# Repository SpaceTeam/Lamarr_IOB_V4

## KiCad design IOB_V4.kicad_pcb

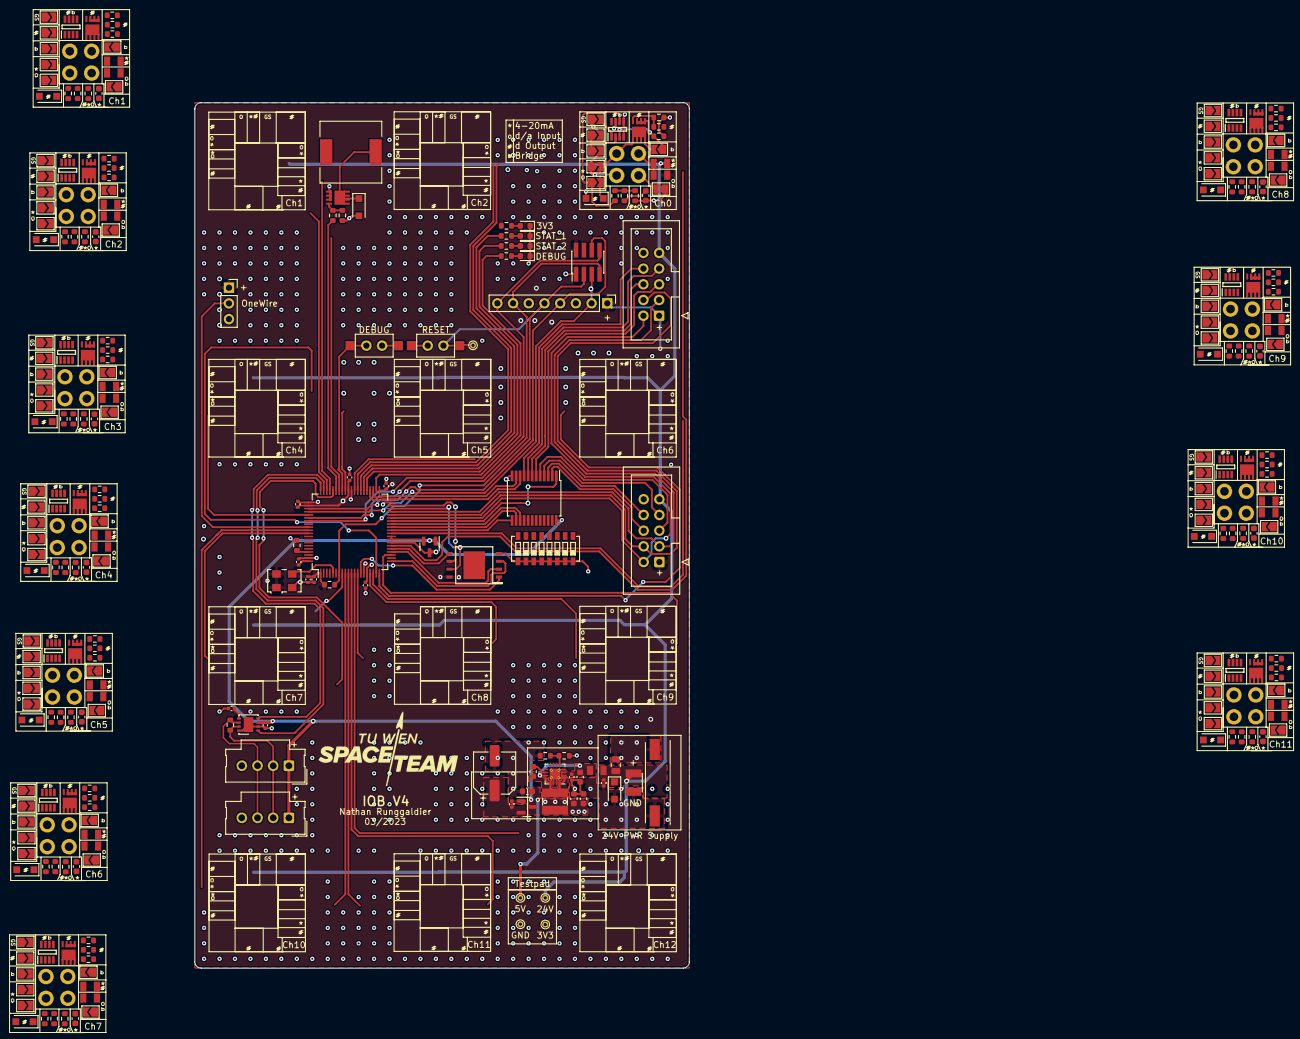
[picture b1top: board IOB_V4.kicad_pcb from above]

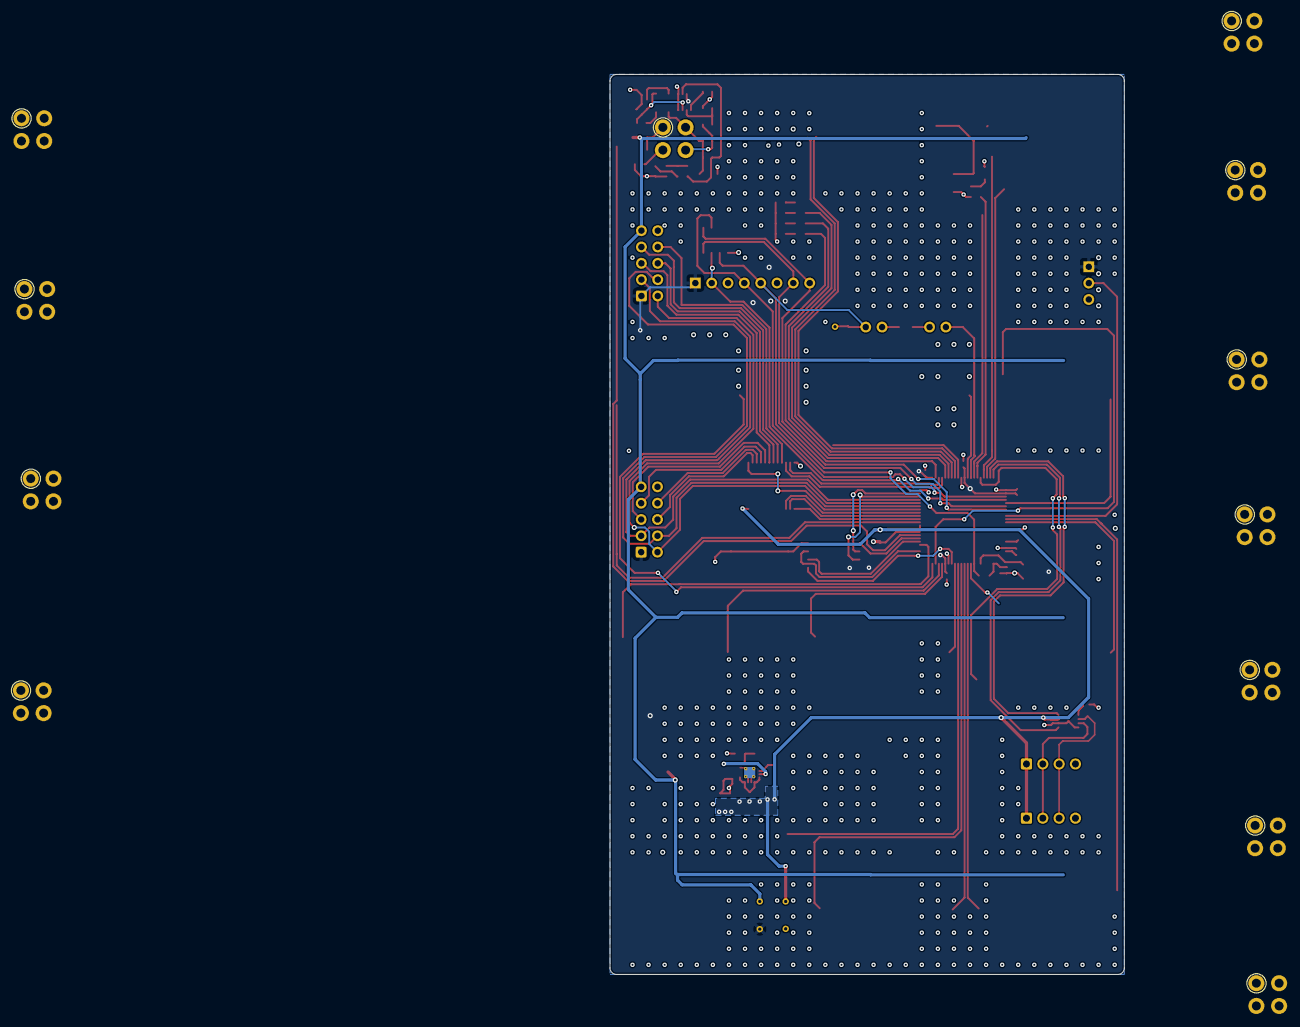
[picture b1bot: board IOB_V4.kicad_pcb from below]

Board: 4 copper layers, 80.0 x 140.0 mm, 305 parts (12 on the bottom side), 207 nets.

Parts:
C1, C3, C9, C10, C11, C12, C13, C15, C16, C17, C18: 100n; C_0402_1005Metric
C2: 22u; C_0805_2012Metric
C4, C8: 10u; C_0603_1608Metric
C5: 100n; C_0603_1608Metric
C6, C7: 22u; C_0603_1608Metric
C14: NP; CP_Elec_6.3x4.9
C19: 4.7u; C_0402_1005Metric
C20, C21, C22, C23, C24, C25, C26, C27, C28, C29, C30, C31: C; C_0603_1608Metric
D1: 30V; D_SOD-123F
D2, D3, D4, D5, D6, D7, D8, D9, D10, D11, D12, D13, D18: D; D_SOD-123F
D14, D15, D16, D17: LED; LED_0603_1608Metric
F1, F2, F3, F4, F5, F6, F7, F8, F9, F10, F11, F12, F13, F14, F15, F16, F17, F18, F19, F20, F21, F22, F23, F24, F25: Polyfuse; 0805L110SL PPTC Polyfuse Littelfuse
G1: SpaceTeam_LOGO; ST_Logo_new
IC1, IC2, IC3, IC4, IC5, IC6, IC7, IC8, IC9, IC10, IC11, IC12: PINA350ABSIDDFR; SOT65P280X110-8N
J1: Conn_01x02; Molex_MicroFit_2Pin_Vertical
J2: Conn_01x03; PinSocket_1x03_P2.54mm_Vertical
J3, J4, J5, J6, J7, J8, J9, J10, J11, J12, J13, J14: Conn_01x04; TE_M12_4_Pin_PCB
J15: Conn_01x08; PinHeader_1x08_P2.54mm_Vertical
J16: Conn_02x04_Odd_Even; PinHeader_2x04_P1.27mm_Vertical_SMD
J17, J19: Conn_01x04; Molex_SL_171971-0004_1x04_P2.54mm_Vertical
J18, J20: Conn_01x10; IDC-Header_2x05_P2.54mm_Vertical
JP1, JP2, JP3, JP4, JP5, JP6, JP7, JP8, JP9, JP10, JP11, JP12, JP13, JP14, JP15, JP16, JP17, JP18, JP19, JP20, JP21, JP22, JP23, JP24, JP25, JP26, JP27, JP28, JP29, JP30, JP31, JP32, JP33, JP34, JP35, JP36, JP37, JP38, JP39, JP40, JP41, JP42, JP43, JP44, JP45, JP46, JP47, JP48, JP49, JP50, JP51, JP52, JP53, JP54, JP55, JP56, JP57, JP58, JP59, JP60, JP61, JP62, JP63, JP64, JP65, JP66, JP67, JP68, JP69, JP70, JP71, JP72, JP73, JP74, JP75, JP76, JP77, JP78, JP79, JP80, JP81, JP82, JP83, JP84: Jumper_2_Open; SolderJumper-2_P1.3mm_Open_TrianglePad1.0x1.5mm
L1: 4.7uH; SRN4018TA-4R7M
LS1: Speaker_Crystal; Piezo_Buzzer
Q1, Q2, Q3, Q4, Q5, Q6, Q7, Q8, Q9, Q10, Q11, Q12, Q13: BSZ0902NSATMA1; PG_TSDSON-8
R1, R7, R13, R19, R25, R31, R37, R43, R49, R55, R61, R67, R85, R86: R; R_0603_1608Metric
R2, R8, R14, R20, R26, R32, R38, R44, R50, R56, R62, R68, R93: 0R; R_0603_1608Metric
R3, R9, R15, R21, R27, R33, R39, R45, R51, R57, R63, R69: NP; R_0603_1608Metric
R4, R10, R16, R22, R28, R34, R40, R46, R52, R58, R64, R70, R73: Rgate; R_0603_1608Metric
R5, R11, R17, R23, R29, R35, R41, R47, R53, R59, R65, R71, R74: Rpull; R_0603_1608Metric
R6, R12, R18, R24, R30, R36, R42, R48, R54, R60, R66, R72: 100m; R_0603_1608Metric
R87, R88, R89, R90, R92: 120R; R_0603_1608Metric
R94: Rpullup; R_0603_1608Metric
SW1, SW2: SW_Push_Dual; SW_SPST_CK_RS282G05A3_and_THT
SW3: SW_DIP_x08; 8_Pin_DIP_Switch
TP1, TP2, TP3, TP4, TP5: TestPoint; TestPoint_THTPad_D1.0mm_Drill0.5mm
U1: REF3033; SOT-23
U2: CD74HC4067SM; SSOP-24_5.3x8.2mm_P0.65mm
U14: TS30041; QFN-16-1EP_3x3mm_P0.5mm_EP1.75x1.75mm_ThermalVias
U15: MCP1700-3302E_SOT23; SOT-23
U17: MCP2562FD; DFN-8-1EP_3x3mm_P0.65mm_EP1.55x2.4mm
U18: W25Q256JV; WSON-8-8x6mm
U19: STM32G474MET3; LQFP-80_12x12mm_P0.5mm
X1: TXC-7C; Oscillator_SMD_TXC_7C-4Pin_5.0x3.2mm

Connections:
+3.3VA: U1.2 (OUT), U19.28 (VREF+), U19.29 (VDDA)
+3V3: C9.1, C10.1, C11.1, C12.1, C14.1, C15.1, C16.1, C17.1, C18.1, C19.1, F2.1, F4.1, F6.1, F8.1, F10.1, F12.1, F14.1, F16.1, F18.1, F20.1, F22.1, F24.1, IC1.7 (V+), IC2.7 (V+), IC3.7 (V+), IC4.7 (V+), IC5.7 (V+), IC6.7 (V+), IC7.7 (V+), IC8.7 (V+), IC9.7 (V+), IC10.7 (V+), IC11.7 (V+), IC12.7 (V+), J2.1, J15.1, J16.2, J18.1, J20.1, R87.1, R94.1, TP3.1, U15.2 (VO), U17.5 (Vio), U18.8 (VCC), U19.1 (VBAT), U19.16 (VDD), U19.41 (VDD), U19.51 (VDD), U19.62 (VDD), U19.80 (VDD), X1.1 (EN), X1.4 (Vdd)
+5V: C6.2, C7.2, C8.1, C13.2, J17.1, J19.1, L1.2, R85.2, TP5.1, U1.1 (IN), U2.24 (VCC), U15.3 (VI), U17.3 (VDD)
+24V: C1.1, C2.1, D1.1 (A1), F1.1, F3.1, F5.1, F7.1, F9.1, F11.1, F13.1, F15.1, F17.1, F19.1, F21.1, F23.1, F25.1, J1.1, J18.9, J20.9, LS1.1, TP4.1
/En0: R70.1, U19.12 (PA0)
/En1: R4.1, U19.58 (PA10)
/En2: R10.1, U19.54 (PC8)
/En3: R16.1, U19.47 (PD8)
/En4: R22.1, U19.65 (PA15)
/En5: R28.1, U19.52 (PC6)
/En6: R34.1, U19.20 (PA6)
/En7: R40.1, U19.71 (PD2)
/En8: R46.1, U19.13 (PA1)
/En9: R52.1, U19.18 (PA4)
/En10: R58.1, U19.70 (PD1)
/En11: R64.1, U19.10 (PC2)
/MCU/ADC1_IN4: C27.1, R43.1, U19.17 (PA3)
/MCU/ADC2_IN11: C28.1, R49.1, U19.23 (PC5)
/MCU/ADC2_IN12: C22.1, R13.1, U19.26 (PB2)
/MCU/ADC2_IN13: C23.1, R19.1, U19.19 (PA5)
/MCU/ADC3_IN4: C25.1, R31.1, U19.30 (PE7)
/MCU/ADC3_IN7: C24.1, R25.1, U19.49 (PD10)
/MCU/ADC5_IN1: C31.1, R67.1, U19.56 (PA8)
/MCU/ADC5_IN2: C20.1, R1.1, U19.57 (PA9)
/MCU/ADC5_IN13: C21.1, R7.1, U19.48 (PD9)
/MCU/ADC12_IN6: C26.1, R37.1, U19.8 (PC0)
/MCU/ADC12_IN7: C29.1, R55.1, U19.9 (PC1)
/MCU/ADC12_IN9: C30.1, R61.1, U19.11 (PC3)
/MCU/BUTTON_1: SW2.2, U19.53 (PC7)
/MCU/CAN1_RX: U17.4 (RXD), U19.59 (PA11)
/MCU/CAN1_TX: U17.1 (TXD), U19.60 (PA12)
/MCU/CANH1: J17.2, J19.2, R92.1, U17.7 (CANH)
/MCU/CANL1: J17.3, J19.3, R92.2, U17.6 (CANL)
/MCU/CLK: U19.5 (PF0-OSC_IN), X1.3 (OUT)
/MCU/DEBUG_LED: R90.1, U19.42 (PB11)
/MCU/MUX1_SEL0: U2.10 (S0), U19.44 (PB13)
/MCU/MUX1_SEL1: U2.11 (S1), U19.43 (PB12)
/MCU/MUX1_SEL2: U2.14 (S2), U19.32 (PE9)
/MCU/MUX1_SEL3: U2.13 (S3), U19.31 (PE8)
/MCU/MUX1_~EN: U2.15 (~E), U19.33 (PE10)
/MCU/NRST: J15.5, J16.3, R94.2, SW1.2, TP2.1, U19.7 (PG10-NRST)
/MCU/QUADSPI1_BK1_IO0: U18.5 (DI(IO0)), U19.25 (PB1)
/MCU/QUADSPI1_BK1_IO1: U18.2 (DO(IO1)), U19.24 (PB0)
/MCU/QUADSPI1_BK1_IO2: U18.3 (~WP(IO2)), U19.21 (PA7)
/MCU/QUADSPI1_BK1_IO3: U18.7 (~RESET(IO3)), U19.38 (PE15)
/MCU/QUADSPI1_BK1_NCS: U18.1 (~CS), U19.14 (PA2)
/MCU/QUADSPI1_CLK: U18.6 (CLK), U19.39 (PB10)
/MCU/SPI4_NSS: U2.1 (COM), U19.34 (PE11)
/MCU/STATUS_LED_1: R88.1, U19.46 (PB15)
/MCU/STATUS_LED_2: R89.1, U19.45 (PB14)
/MCU/SWCLK: J15.2, J16.5, U19.64 (PA14)
/MCU/SWDIO: J15.4, J16.6, U19.63 (PA13)
/MCU/Speaker_1: R73.1, U19.55 (PC9)
/MCU/UART4_RX: J15.8, J16.8, U19.67 (PC11)
/MCU/UART4_TX: J15.7, J16.7, U19.66 (PC10)
/OneWire: J2.2, U19.69 (PD0)
/SPI4_CLK: J18.2, J20.2, U19.35 (PE12)
/SPI4_MISO: J18.4, J20.4, U19.36 (PE13)
/SPI4_MOSI: J18.3, J20.3, U19.37 (PE14)
/SPI4_NSS1: J20.5, U2.6 (I3)
/SPI4_NSS2: J20.6, U2.7 (I2)
/SPI4_NSS3: J20.7, U2.8 (I1)
/SPI4_NSS4: J20.8, U2.9 (I0)
/SPI4_NSS5: J18.5, U2.5 (I4)
/SPI4_NSS6: J18.6, U2.2 (I7)
/SPI4_NSS7: J18.7, U2.4 (I5)
/SPI4_NSS8: J18.8, U2.3 (I6)
GND: C1.2, C2.2, C3.1, C4.1, C6.1, C7.1, C8.2, C9.2, C10.2, C11.2, C12.2, C13.1, C14.2, C15.2, C16.2, C17.2, C18.2, C19.2, C20.2, C21.2, C22.2, C23.2, C24.2, C25.2, C26.2, C27.2, C28.2, C29.2, C30.2, C31.2, D1.2 (A2), D2.2 (A), D3.2 (A), D4.2 (A), D5.2 (A), D6.2 (A), D7.2 (A), D8.2 (A), D9.2 (A), D10.2 (A), D11.2 (A), D12.2 (A), D13.2 (A), D14.1 (K), D15.1 (K), D16.1 (K), D17.1 (K), D18.2 (A), IC1.4 (V-), IC1.5 (REF), IC2.4 (V-), IC2.5 (REF), IC3.4 (V-), IC3.5 (REF), IC4.4 (V-), IC4.5 (REF), IC5.4 (V-), IC5.5 (REF), IC6.4 (V-), IC6.5 (REF), IC7.4 (V-), IC7.5 (REF), IC8.4 (V-), IC8.5 (REF), IC9.4 (V-), IC9.5 (REF), IC10.4 (V-), IC10.5 (REF), IC11.4 (V-), IC11.5 (REF), IC12.4 (V-), IC12.5 (REF), J1.2, J1.MP (MountPin), J2.3, J15.3, J16.1, J17.4, J18.10, J19.4, J20.10, JP1.1 (A), JP4.2 (B), JP7.1 (A), JP8.1 (A), JP11.2 (B), JP14.1 (A), JP15.1 (A), JP18.2 (B), JP21.1 (A), JP22.1 (A), JP25.2 (B), JP28.1 (A), JP29.1 (A), JP32.2 (B), JP35.1 (A), JP36.1 (A), JP39.2 (B), JP42.1 (A), JP43.1 (A), JP46.2 (B), JP49.1 (A), JP50.1 (A), JP53.2 (B), JP56.1 (A), JP57.1 (A), JP60.2 (B), JP63.1 (A), JP64.1 (A), JP67.2 (B), JP70.1 (A), JP71.1 (A), JP74.2 (B), JP77.1 (A), JP78.1 (A), JP81.2 (B), JP84.1 (A), Q13.1 (S), R3.2, R5.2, R6.2, R9.2, R11.2, R12.2, R15.2, R17.2, R18.2, R21.2, R23.2, R24.2, R27.2, R29.2, R30.2, R33.2, R35.2, R36.2, R39.2, R41.2, R42.2, R45.2, R47.2, R48.2, R51.2, R53.2, R54.2, R57.2, R59.2, R60.2, R63.2, R65.2, R66.2, R69.2, R71.2, R72.2, R74.2, R86.2, R93.1, SW1.1, SW2.1, SW3.1, SW3.2, SW3.3, SW3.4, SW3.5, SW3.6, SW3.7, SW3.8, TP1.1, U1.3 (GND), U2.12 (GND), U14.4 (GND), U14.14 (PGND), U14.15 (PGND), U14.17 (PAD), U15.1 (GND), U17.2 (VSS), U17.8 (SHDN), U17.9 (PAD), U18.4 (GND), U19.15 (VSS), U19.27 (VSSA), U19.40 (VSS), U19.50 (VSS), U19.61 (VSS), U19.79 (VSS), X1.2 (GND)
unnamed: C3.2, C4.2, F25.2, U14.2 (VCC), U14.3 (VCC), U14.11 (VCC)
unnamed: C5.1, L1.1, U14.1 (VSW), U14.12 (VSW), U14.13 (VSW), U14.16 (VSW)
unnamed: C5.2, U14.10 (BST)
unnamed: D2.1 (K), J3.2, JP2.2 (B), JP3.2 (B), JP5.2 (B), Q1.3 (D)
unnamed: D3.1 (K), J4.2, JP9.2 (B), JP10.2 (B), JP12.2 (B), Q2.3 (D)
unnamed: D4.1 (K), J5.2, JP16.2 (B), JP17.2 (B), JP19.2 (B), Q3.3 (D)
unnamed: D5.1 (K), J6.2, JP23.2 (B), JP24.2 (B), JP26.2 (B), Q4.3 (D)
unnamed: D6.1 (K), J7.2, JP30.2 (B), JP31.2 (B), JP33.2 (B), Q5.3 (D)
unnamed: D7.1 (K), J8.2, JP37.2 (B), JP38.2 (B), JP40.2 (B), Q6.3 (D)
unnamed: D8.1 (K), J9.2, JP44.2 (B), JP45.2 (B), JP47.2 (B), Q7.3 (D)
unnamed: D9.1 (K), J10.2, JP51.2 (B), JP52.2 (B), JP54.2 (B), Q8.3 (D)
unnamed: D10.1 (K), J11.2, JP58.2 (B), JP59.2 (B), JP61.2 (B), Q9.3 (D)
unnamed: D11.1 (K), J12.2, JP65.2 (B), JP66.2 (B), JP68.2 (B), Q10.3 (D)
unnamed: D12.1 (K), J13.2, JP72.2 (B), JP73.2 (B), JP75.2 (B), Q11.3 (D)
unnamed: D13.1 (K), J14.2, JP79.2 (B), JP80.2 (B), JP82.2 (B), Q12.3 (D)
unnamed: D14.2 (A), R87.2
unnamed: D15.2 (A), R88.2
unnamed: D16.2 (A), R89.2
unnamed: D17.2 (A), R90.2
unnamed: D18.1 (K), LS1.2, Q13.3 (D)
unnamed: F1.2, F2.2, J3.1
unnamed: F3.2, F4.2, J4.1
unnamed: F5.2, F6.2, J5.1
unnamed: F7.2, F8.2, J6.1
unnamed: F9.2, F10.2, J7.1
unnamed: F11.2, F12.2, J8.1
unnamed: F13.2, F14.2, J9.1
unnamed: F15.2, F16.2, J10.1
unnamed: F17.2, F18.2, J11.1
unnamed: F19.2, F20.2, J12.1
unnamed: F21.2, F22.2, J13.1
unnamed: F23.2, F24.2, J14.1
unnamed: IC1.1 (GS), JP1.2 (B)
unnamed: IC1.2 (IN-), JP4.1 (A), JP6.1 (A)
unnamed: IC1.3 (IN+), JP3.1 (A), Q1.1 (S), R6.1
unnamed: IC1.6 (OUT), JP2.1 (A), R2.1
unnamed: IC2.1 (GS), JP8.2 (B)
unnamed: IC2.2 (IN-), JP11.1 (A), JP13.1 (A)
unnamed: IC2.3 (IN+), JP10.1 (A), Q2.1 (S), R12.1
unnamed: IC2.6 (OUT), JP9.1 (A), R8.1
unnamed: IC3.1 (GS), JP15.2 (B)
unnamed: IC3.2 (IN-), JP18.1 (A), JP20.1 (A)
unnamed: IC3.3 (IN+), JP17.1 (A), Q3.1 (S), R18.1
unnamed: IC3.6 (OUT), JP16.1 (A), R14.1
unnamed: IC4.1 (GS), JP22.2 (B)
unnamed: IC4.2 (IN-), JP25.1 (A), JP27.1 (A)
unnamed: IC4.3 (IN+), JP24.1 (A), Q4.1 (S), R24.1
unnamed: IC4.6 (OUT), JP23.1 (A), R20.1
unnamed: IC5.1 (GS), JP29.2 (B)
unnamed: IC5.2 (IN-), JP32.1 (A), JP34.1 (A)
unnamed: IC5.3 (IN+), JP31.1 (A), Q5.1 (S), R30.1
unnamed: IC5.6 (OUT), JP30.1 (A), R26.1
unnamed: IC6.1 (GS), JP36.2 (B)
unnamed: IC6.2 (IN-), JP39.1 (A), JP41.1 (A)
unnamed: IC6.3 (IN+), JP38.1 (A), Q6.1 (S), R36.1
unnamed: IC6.6 (OUT), JP37.1 (A), R32.1
unnamed: IC7.1 (GS), JP43.2 (B)
unnamed: IC7.2 (IN-), JP46.1 (A), JP48.1 (A)
unnamed: IC7.3 (IN+), JP45.1 (A), Q7.1 (S), R42.1
unnamed: IC7.6 (OUT), JP44.1 (A), R38.1
unnamed: IC8.1 (GS), JP50.2 (B)
unnamed: IC8.2 (IN-), JP53.1 (A), JP55.1 (A)
unnamed: IC8.3 (IN+), JP52.1 (A), Q8.1 (S), R48.1
unnamed: IC8.6 (OUT), JP51.1 (A), R44.1
unnamed: IC9.1 (GS), JP57.2 (B)
unnamed: IC9.2 (IN-), JP60.1 (A), JP62.1 (A)
unnamed: IC9.3 (IN+), JP59.1 (A), Q9.1 (S), R54.1
unnamed: IC9.6 (OUT), JP58.1 (A), R50.1
unnamed: IC10.1 (GS), JP64.2 (B)
unnamed: IC10.2 (IN-), JP67.1 (A), JP69.1 (A)
unnamed: IC10.3 (IN+), JP66.1 (A), Q10.1 (S), R60.1
unnamed: IC10.6 (OUT), JP65.1 (A), R56.1
unnamed: IC11.1 (GS), JP71.2 (B)
unnamed: IC11.2 (IN-), JP74.1 (A), JP76.1 (A)
unnamed: IC11.3 (IN+), JP73.1 (A), Q11.1 (S), R66.1
unnamed: IC11.6 (OUT), JP72.1 (A), R62.1
unnamed: IC12.1 (GS), JP78.2 (B)
unnamed: IC12.2 (IN-), JP81.1 (A), JP83.1 (A)
unnamed: IC12.3 (IN+), JP80.1 (A), Q12.1 (S), R72.1
unnamed: IC12.6 (OUT), JP79.1 (A), R68.1
unnamed: J3.3, JP5.1 (A), JP6.2 (B)
unnamed: J3.4, JP7.2 (B)
unnamed: J4.3, JP12.1 (A), JP13.2 (B)
unnamed: J4.4, JP14.2 (B)
unnamed: J5.3, JP19.1 (A), JP20.2 (B)
unnamed: J5.4, JP21.2 (B)
unnamed: J6.3, JP26.1 (A), JP27.2 (B)
unnamed: J6.4, JP28.2 (B)
unnamed: J7.3, JP33.1 (A), JP34.2 (B)
unnamed: J7.4, JP35.2 (B)
unnamed: J8.3, JP40.1 (A), JP41.2 (B)
unnamed: J8.4, JP42.2 (B)
unnamed: J9.3, JP47.1 (A), JP48.2 (B)
unnamed: J9.4, JP49.2 (B)
unnamed: J10.3, JP54.1 (A), JP55.2 (B)
unnamed: J10.4, JP56.2 (B)
unnamed: J11.3, JP61.1 (A), JP62.2 (B)
unnamed: J11.4, JP63.2 (B)
unnamed: J12.3, JP68.1 (A), JP69.2 (B)
unnamed: J12.4, JP70.2 (B)
unnamed: J13.3, JP75.1 (A), JP76.2 (B)
unnamed: J13.4, JP77.2 (B)
unnamed: J14.3, JP82.1 (A), JP83.2 (B)
unnamed: J14.4, JP84.2 (B)
unnamed: Q1.2 (G), R4.2, R5.1
unnamed: Q2.2 (G), R10.2, R11.1
unnamed: Q3.2 (G), R16.2, R17.1
unnamed: Q4.2 (G), R22.2, R23.1
unnamed: Q5.2 (G), R28.2, R29.1
unnamed: Q6.2 (G), R34.2, R35.1
unnamed: Q7.2 (G), R40.2, R41.1
unnamed: Q8.2 (G), R46.2, R47.1
unnamed: Q9.2 (G), R52.2, R53.1
unnamed: Q10.2 (G), R58.2, R59.1
unnamed: Q11.2 (G), R64.2, R65.1
unnamed: Q12.2 (G), R70.2, R71.1
unnamed: Q13.2 (G), R73.2, R74.1
unnamed: R1.2, R2.2, R3.1
unnamed: R7.2, R8.2, R9.1
unnamed: R13.2, R14.2, R15.1
unnamed: R19.2, R20.2, R21.1
unnamed: R25.2, R26.2, R27.1
unnamed: R31.2, R32.2, R33.1
unnamed: R37.2, R38.2, R39.1
unnamed: R43.2, R44.2, R45.1
unnamed: R49.2, R50.2, R51.1
unnamed: R55.2, R56.2, R57.1
unnamed: R61.2, R62.2, R63.1
unnamed: R67.2, R68.2, R69.1
unnamed: R85.1, R86.1, U14.5 (FB)
unnamed: R93.2, U19.77 (PB8-BOOT0)
unnamed: SW3.9, U2.23 (I8)
unnamed: SW3.10, U2.22 (I9)
unnamed: SW3.11, U2.21 (I10)
unnamed: SW3.12, U2.20 (I11)
unnamed: SW3.13, U2.19 (I12)
unnamed: SW3.14, U2.18 (I13)
unnamed: SW3.15, U2.17 (I14)
unnamed: SW3.16, U2.16 (I15)

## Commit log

2023-02-25 Initial + select lines removed
2023-02-25 Speaker Voltage fixed
2023-02-25 Can connector pinout fix
2023-02-25 Correct MUX Footprint added
2023-02-27 Circuit fix
2023-02-27 Pictures added
2023-02-27 Annotation fix
2023-02-28 Footprint separation
2023-02-28 Connector layout V1
    1 of the channels has been set
2023-02-28 Ch config set, not yet routed
2023-02-28 Routing complete ex. dip switch
2023-02-28 Routing complete ex. dip switch & stitching
2023-02-28 DRC fix
2023-02-28 Stitching WIP
2023-03-01 UART5 add
2023-03-01 DIP Switch fix
2023-03-01 Final check done
2023-03-01 TXV push fix
2023-03-13 Almost ready to be ordered
2023-03-15 Added Servo Config
2023-03-16 IOBv4 JLCPCB ordered on 15.03.2023
